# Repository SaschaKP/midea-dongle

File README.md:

# Midea WiFi Dongle - v3

This repo is a complete rework of [Rene Klootwijk's repository](https://github.com/reneklootwijk/mideahvac-dongle). So credits for the initial hardware study and design go to him!

I've made a lot of changes to the board:
* the board will fit inside the original spacer, occuping the original space, but without casing
* all pads can be soldered with hot-air gun and soldering paste, they are slightly larger for that purpose in mind
* it uses an ESP32 C6 and the software for making it work with this dongle (esphome) can be found [in my repository](https://github.com/SaschaKP/esphome-midea-direct)
* Converted the KiCad project to KiCad 9

For this particular repository you can use an ESP32 C6 MINI (WT0132C6-S5) that can be used as a drop-in replacement for ESP-12F

That's what the board now looks like:

## PCB and Parts
* The buttons are 3x4mm in size. Height is up to your liking. Can easily be found on AliExpress:

* Specs of the USB jack, can also be found on AliExpress:

* LDO Caps (C1 & C2) can be either tantalum or ceramic: Officially should be tantalum, but ceramic work just fine. 
* Remember that the WT0132C6-S5 (ESP32 C6 MINI) is interchangeable with ESP-12F or ESP-07 which offers an external antenna:

I **highly** recommend taking a look at the iBOM file that can also be found in the "production-files" folder. It makes sourcing the parts and soldering so much easier!

## Making of PCB
You will find some files to print for classic paper-toner-iron transfer on copper for etching, or you can also use a more modern approach with a 3D printer (with 0.25 or less nozzle) with spray painting or top of the model to track the negative part, etching as usual with acid and subsequent protective paint upon tracks to avoid potential short circuits later.
If you are familiar with this kind of prototyping you will find what you need inside the print_file directory

## Flashing
Flashing the ESP can be done using any USB-to-UART adapter. I recommend getting an USB-A-socket cable with open ends, so you can crimp a dupont at the open end.
So TX from the dongle goes to RX on the UART adapter and RX from the dongle goes to TX on the UART adapter. Set the UART adapter to 5V. Yes, it is safe. You will **not** burn the ESP in this case! The board has two mosfets that will switch the pins to 3v3.
Now how to actually flash the board:
 1. Create a new device under "ESPHome Builder" in Home Assistant. Choose `ESP32 C6 devkitm` as board
 2. You can find an example config under "esphome". Edit the config in ESPHome builder and substitute the placeholders and potentially the board.
 3. Install and download.
 4. Now open [ESPHome Web](https://web.esphome.io)
 5. Connect the UART adapter to your PC, but not the dongle just yet!
 6. Hold the "PRG" button on the dongle and keep holding it!
 7. Now connect the dongle to the UART adapter.
 8. Click "Connect" on ESPHome Web, select the UART adapter, click "Install", select the bin you've just built and downloaded and flash it.
 9. As soon as it says "Erasing" or "Flashing", you can release the "PRG" button.
 10. Wait  for it to be installed and it will show up in your Wi-Fi and under "Devices" in Home Assistant

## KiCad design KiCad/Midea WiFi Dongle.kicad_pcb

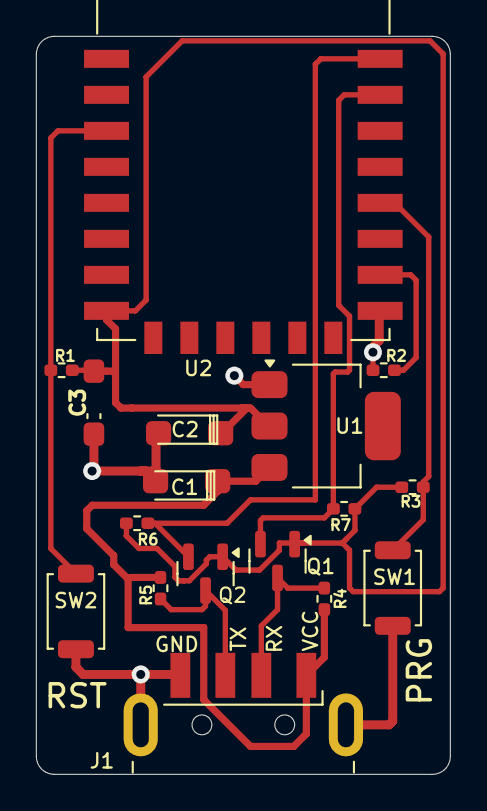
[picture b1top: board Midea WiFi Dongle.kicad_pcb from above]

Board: 2 copper layers, 23.0 x 41.0 mm, 18 parts (1 on the bottom side), 10 nets.

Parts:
C1, C2: 22uF; CP_1.62x0.84mm_0603_1608metric_HandSolder
C3: 100nF; CP_1.62x0.84mm_0603_1608Metric
G1: LOGO; Yoshi-Egg-Small
J1: USB_A; USB_A_CNCTech_1001-011-01101_Horizontal
Q1, Q2: BSS138; SOT-23
R1, R2, R3, R4, R5, R6, R7: 10k; R_0402_1005Metric_Pad0.72x0.64mm_HandSolder
SW1, SW2: SW_Push; SW_Push_SPST_NO_Alps_SKRK
U1: AMS1117-3.3; SOT-223
U2: WT0132C6-S5

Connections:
+3V3: C2.1, C3.2, Q1.1 (G), Q2.1 (G), R1.2, R3.2, R6.2, R7.1, U1.2 (VO), U2.8 (VCC)
+5V: C1.1, J1.1 (VBUS), R4.2, R5.1, U1.3 (VI)
/EN: R1.1, SW2.2, U2.3 (EN)
/GPIO7: R2.1, U2.16 (GPIO7)
/GPIO9: R3.1, SW1.2, U2.18 (GPIO9)
/RN1-5: Q2.2 (S), R6.1, U2.22 (GPIO16/TXD)
/RN1-6: Q1.2 (S), R7.2, U2.21 (GPIO17/RXD)
/RX_USB: J1.2 (D-), Q1.3 (D), R4.1
/TX_USB: J1.3 (D+), Q2.3 (D), R5.2
GND: C1.2, C2.2, C3.1, J1.4 (GND), J1.5 (Shield), R2.2, SW1.1, SW2.1, U1.1 (GND), U2.15 (GND)

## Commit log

2025-11-15 correct image paths
2025-11-15 dongle photo
2025-11-17 Added BMP (for traditional, toner, paper, iron method) and STL (negative, for 3D printer method, with spray paint, requires 0.25mm nozzle)
2025-11-17 add holes for usb jack
2025-11-17 Adding 3D print file for tracks coating/protective layer
2025-11-17 3d model image
2025-12-01 updated 3D model, I have to update the 3D printing model too.
